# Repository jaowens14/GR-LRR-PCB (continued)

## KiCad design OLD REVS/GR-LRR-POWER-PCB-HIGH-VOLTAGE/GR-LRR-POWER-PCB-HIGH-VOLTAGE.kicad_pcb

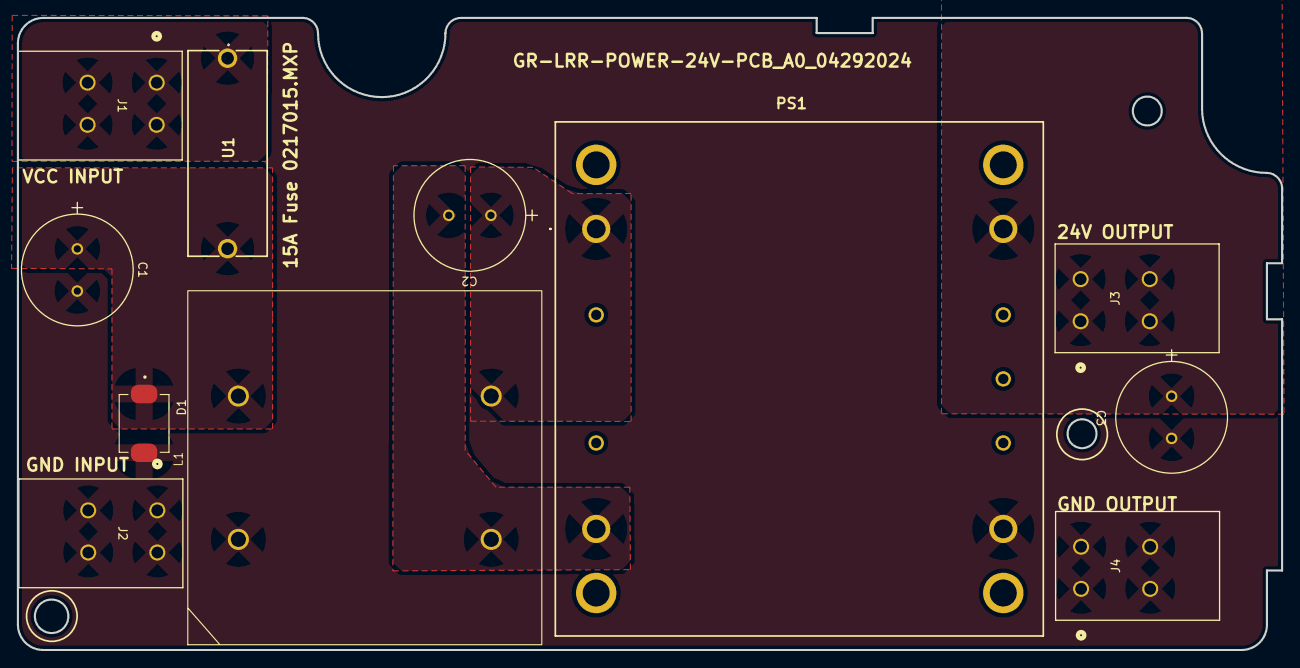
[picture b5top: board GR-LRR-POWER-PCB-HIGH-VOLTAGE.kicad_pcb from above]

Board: 2 copper layers, 150.0 x 75.0 mm, 11 parts (0 on the bottom side), 6 nets, no tracks yet.

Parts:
C1, C2, C3: 100PX220MEFC12.5X20; CAP_PK&slash_PZ_12P5X20_LOW_RUB
D1: SMCJ40A; DIOM7959X262N
J1: BATT+; 2604
J2, J4: GND; 2604
J3: 24V; 2604
L1: SC-14-15JH
PS1: QSB30024S24
U1: 696108003002; WR-FSH_THT_2

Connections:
+24V: C3.1, J3.1_1, J3.1_2, J3.2_1, J3.2_2, PS1.9 (+VOUT)
BATT+: C1.1, D1.C, L1.2 (1N2), U1.2
GND: C1.2, C3.2, D1.A, J2.1_1, J2.1_2, J2.2_1, J2.2_2, J4.1_1, J4.1_2, J4.2_1, J4.2_2, L1.1 (1N1), PS1.5 (-VOUT)
unnamed: J1.1_1, J1.1_2, J1.2_1, J1.2_2, U1.1
unnamed: C2.2, L1.4 (2N1), PS1.4 (-VIN)
unnamed: C2.1, L1.3 (2N2), PS1.1 (+VIN)
